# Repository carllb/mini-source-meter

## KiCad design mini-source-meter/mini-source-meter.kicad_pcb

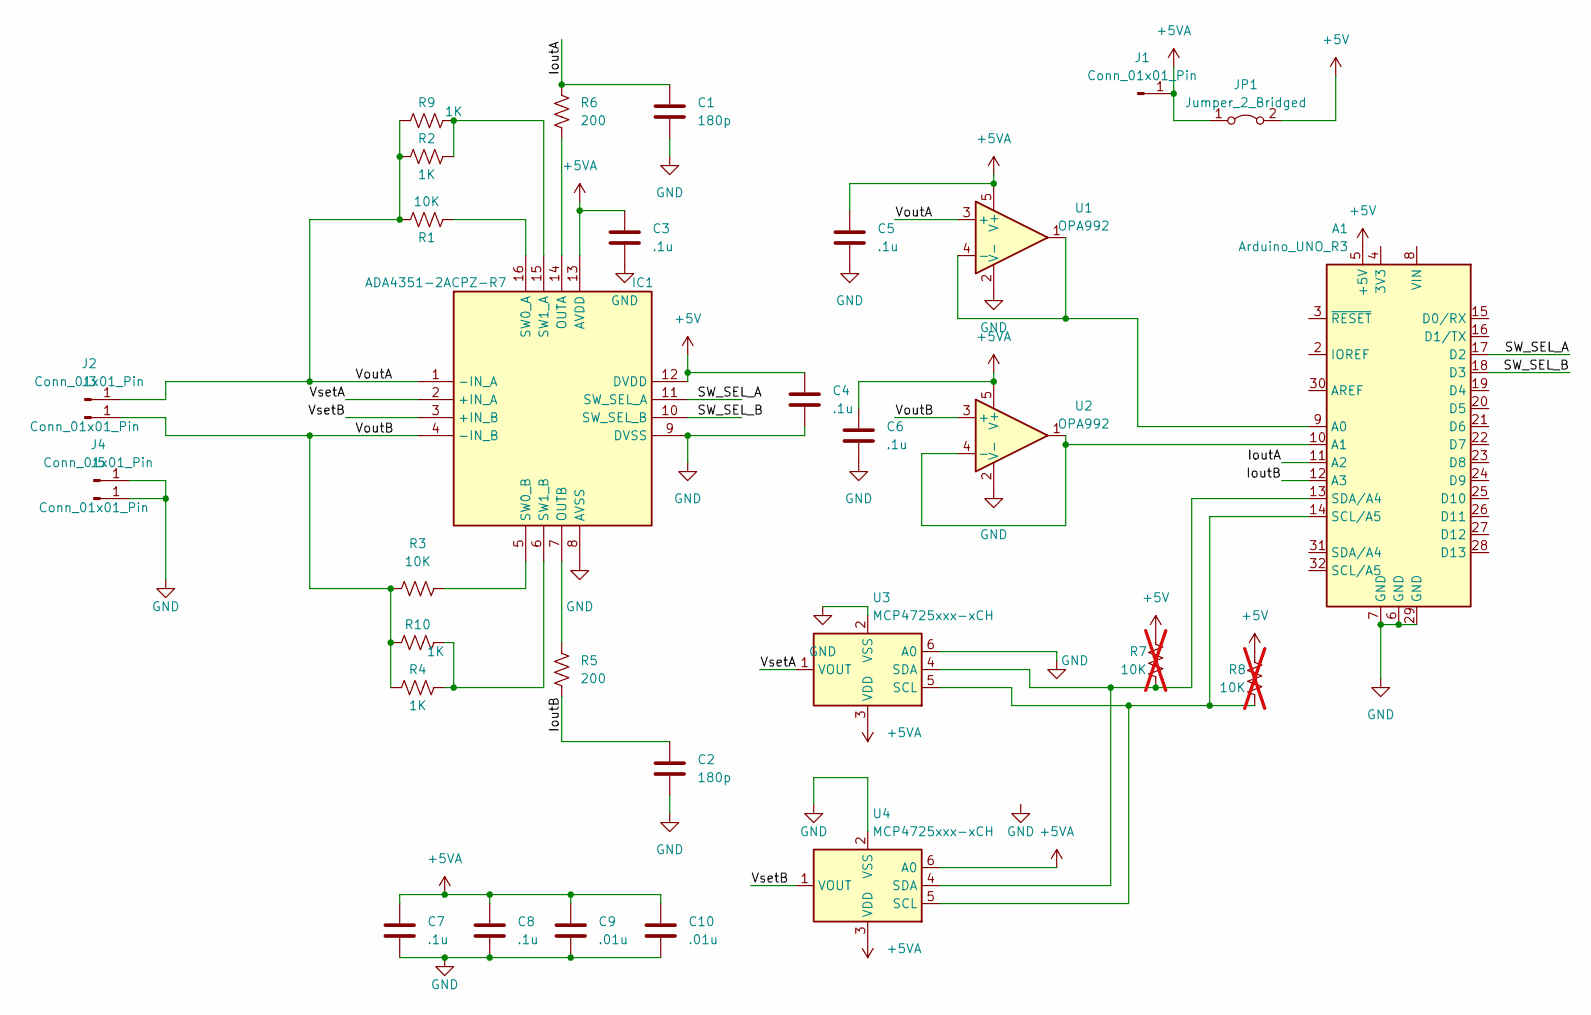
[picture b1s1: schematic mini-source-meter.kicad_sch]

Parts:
A1: Arduino_UNO_R3
C1, C2: 180p; C_0805_2012Metric_Pad1.18x1.45mm_HandSolder
C3, C4, C5, C6, C7, C8: .1u; C_0603_1608Metric_Pad1.08x0.95mm_HandSolder
C9, C10: .01u; C_0603_1608Metric_Pad1.08x0.95mm_HandSolder
IC1: ADA4351-2ACPZ-R7; QFN50P300X300X80-16N-D; Manufacturer_Part_Number ADA4351-2ACPZ-R7
J1, J2, J3, J4, J5: Conn_01x01_Pin; PinHeader_1x01_P2.54mm_Vertical
JP1: Jumper_2_Bridged; SolderJumper-2_P1.3mm_Open_Pad1.0x1.5mm
R1, R3: 10K; R_1206_3216Metric_Pad1.30x1.75mm_HandSolder
R2, R4, R9, R10: 1K; R_0805_2012Metric_Pad1.20x1.40mm_HandSolder
R5, R6: 200; R_0805_2012Metric_Pad1.20x1.40mm_HandSolder
R7, R8: 10K; R_1206_3216Metric_Pad1.30x1.75mm_HandSolder; not fitted
U1, U2: OPA992; SOT-23-5
U3, U4: MCP4725xxx-xCH; SOT-23-6

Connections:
+5V: A1.5 (+5V), C4.1, IC1.12 (DVDD), JP1.2 (B), R7.2, R8.2
+5VA: C3.1, C5.1, C6.1, C7.1, C8.1, C9.1, C10.1, IC1.13 (AVDD), J1.1, JP1.1 (A), U1.5 (V+), U2.5 (V+), U3.3 (VDD), U4.3 (VDD), U4.6 (A0)
/IoutA: A1.11 (A2), C1.1, R6.2
/IoutB: A1.12 (A3), C2.1, R5.1
/SW_SEL_A: A1.17 (D2), IC1.11 (SW_SEL_A)
/SW_SEL_B: A1.18 (D3), IC1.10 (SW_SEL_B)
/VoutA: IC1.1 (-IN_A), J2.1, R1.1, R2.2, R9.2, U1.3 (+)
/VoutB: IC1.4 (-IN_B), J3.1, R3.1, R4.2, R10.2, U2.3 (+)
/VsetA: IC1.2 (+IN_A), U3.1 (VOUT)
/VsetB: IC1.3 (+IN_B), U4.1 (VOUT)
GND: A1.6 (GND), A1.7 (GND), A1.29 (GND), C1.2, C2.2, C3.2, C4.2, C5.2, C6.2, C7.2, C8.2, C9.2, C10.2, IC1.8 (AVSS), IC1.9 (DVSS), J4.1, J5.1, U1.2 (V-), U2.2 (V-), U3.2 (VSS), U3.6 (A0), U4.2 (VSS)
unnamed: A1.9 (A0), U1.1, U1.4 (-)
unnamed: A1.10 (A1), U2.1, U2.4 (-)
unnamed: IC1.14 (OUTA), R6.1
unnamed: IC1.7 (OUTB), R5.2
unnamed: IC1.16 (SW0_A), R1.2
unnamed: IC1.5 (SW0_B), R3.2
unnamed: IC1.15 (SW1_A), R2.1, R9.1
unnamed: IC1.6 (SW1_B), R4.1, R10.1
unnamed: A1.14 (SCL/A5), R8.1, U3.5 (SCL), U4.5 (SCL)
unnamed: A1.13 (SDA/A4), R7.1, U3.4 (SDA), U4.4 (SDA)

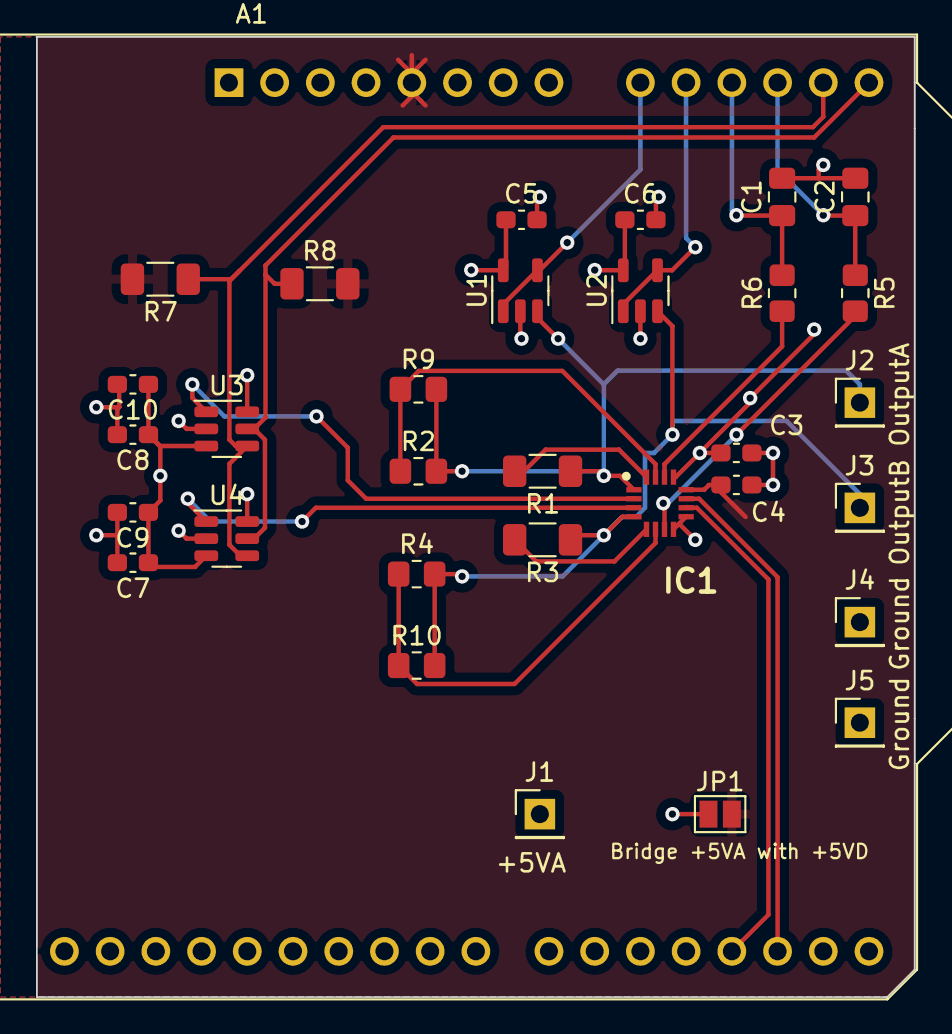
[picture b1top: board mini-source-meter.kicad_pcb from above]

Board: 4 copper layers, 48.8 x 53.3 mm, 32 parts (0 on the bottom side), 21 nets.

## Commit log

2024-01-18 fixed DAC power rails in schmatic
    place and routed components on layout
2024-01-18 moved a trace
